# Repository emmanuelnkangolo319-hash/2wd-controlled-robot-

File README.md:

# 2wd-controlled-robot-
This is a 2 wheeled robot that is built for emergency, but for now it basic funcions are to move and send camera feed.

This build is probably going to take alot out of me, but i think it is possible.
Im doing this because after watching countless videos of firefighters talking to traumatized citizen, they cant get real numbers, like how many people are still inside, in which rooms, if they had these numbers, it would decrease the risk in those operations

The electronics:

Getting the pcb is optional, but i will add it to the bom.csv file with the perf board

The part that im scared will fail, is the ir sensors. I found out that the range of these things is about 10 meters which is good, but while simulating this in Tinkercad, it was slow, im hoping that its just software problems on Tinkercads side.

The 3d model before:

The 3d model after:

Here is why i bumped up the funding, its this part here, think is my first time 3d modeling something that i will actually print. So im obviously prepared to fail, im just hoping that i can fail once, and quick.
Im only going through problems with the mechanical side, which is good i guess, ill try add more of the problems and how i solve them soon

Okay, i finished doing v2 of the 3d model. i made these changes to mainly decrease the weight of the build
v2:

If you want to install the .step file please download the 2wd robot assembly.zip file in the 3d model folder. 

the onshape link:
https://cad.onshape.com/documents/f42b43e04c4ad61b668f94ef/w/0c0e8b55c16ce46e2c956fe2/e/7b67a350074c013e1080d5fa?renderMode=0&uiState=6aca5459fa34469a809cf6e1
(if you are unable to click on the link, just copy and paste it into your web browser)

Build plan:
this section will cover how to build this, i will show a video soon(please go to 3d model/Assembly 1 for more info).
1. Sand the wheels down, both the insides and outsides
2. Brush on one thin layer of epoxy resin on the outside of the wheels
3. Place your carbon fiber sheets on the outside of the wheels where you applied the epoxy
4. Add one more layer of epoxy on top and check the kit to see how long it should cure
5. After letting it cure. in the insides of the wheels, add some glue(super glue/hot glue). Then carfully put the foam inside, trying to go from the center to the edges of the wheel
6. last part will be showing you how to put the electronics in, and the foam for shock absorption

Updating soon.. bye for now

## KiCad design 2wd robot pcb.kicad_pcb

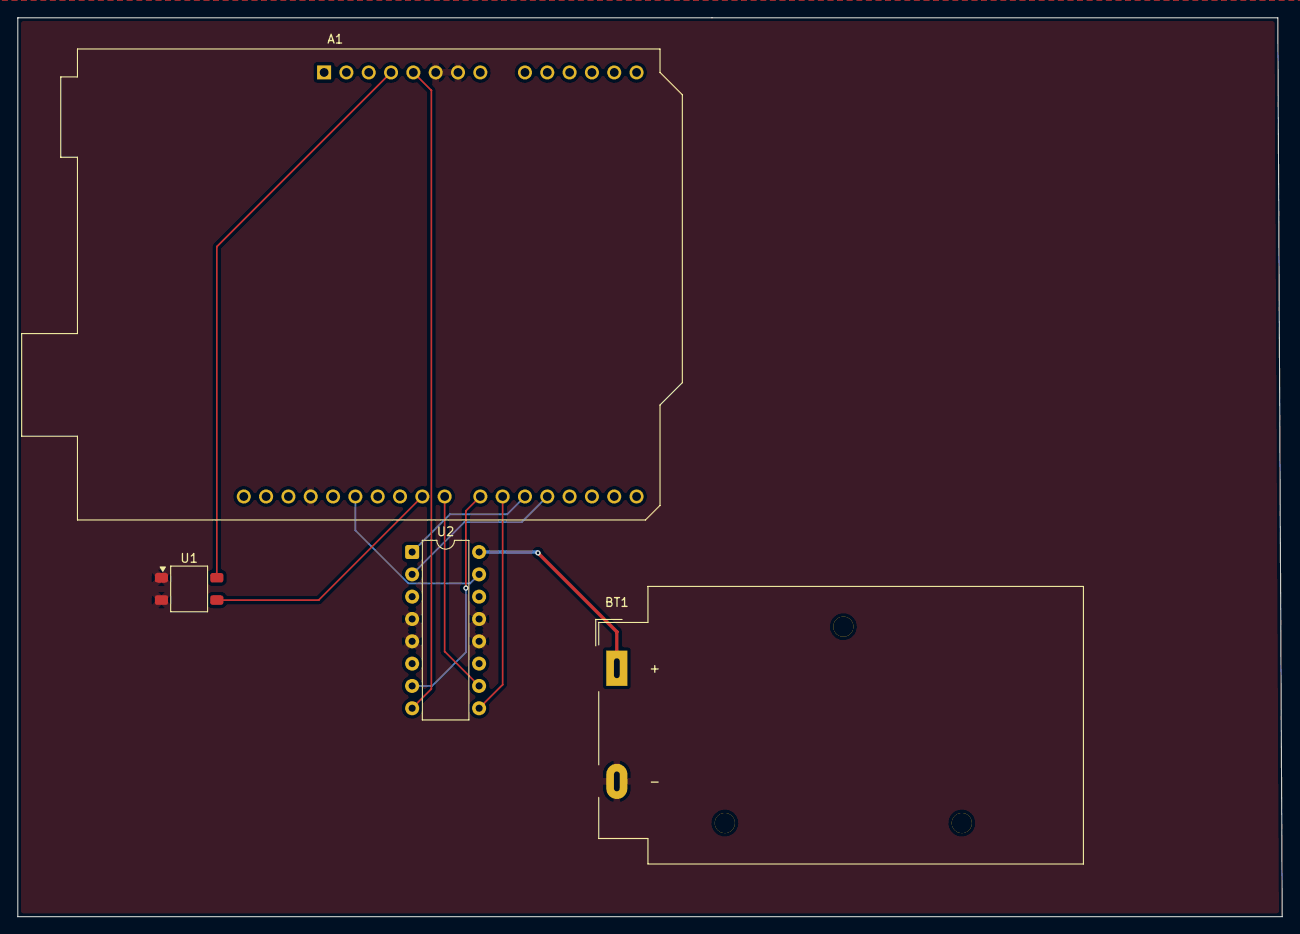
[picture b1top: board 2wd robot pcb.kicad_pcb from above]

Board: 4 copper layers, 143.9 x 102.3 mm, 4 parts (0 on the bottom side), 11 nets.

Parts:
A1: Arduino_UNO_R3
BT1: 9v; BatteryHolder_MPD_BA9VPC_1xPP3
U1: IRM-H6xxT; Everlight_IRM-H6xxT
U2: L293D; DIP-16_W7.62mm

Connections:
GND: A1.6 (GND), A1.7 (GND), A1.29 (GND), BT1.2 (-), U1.1 (GND), U1.2 (GND), U2.4 (GND), U2.5 (GND), U2.12 (GND), U2.13 (GND)
unnamed: A1.4 (3V3), U1.4 (Vcc)
unnamed: A1.5 (+5V), U2.8 (VCC2)
unnamed: A1.19 (D4), U2.2 (1A)
unnamed: A1.20 (D5), U2.1 (EN1,2)
unnamed: A1.21 (D6), U2.9 (EN3,4)
unnamed: A1.22 (D7), U2.7 (2A)
unnamed: A1.23 (D8), U2.10 (3A)
unnamed: A1.24 (D9), U1.3 (OUT)
unnamed: A1.27 (D12), U2.15 (4A)
unnamed: BT1.1 (+), U2.16 (VCC1)
